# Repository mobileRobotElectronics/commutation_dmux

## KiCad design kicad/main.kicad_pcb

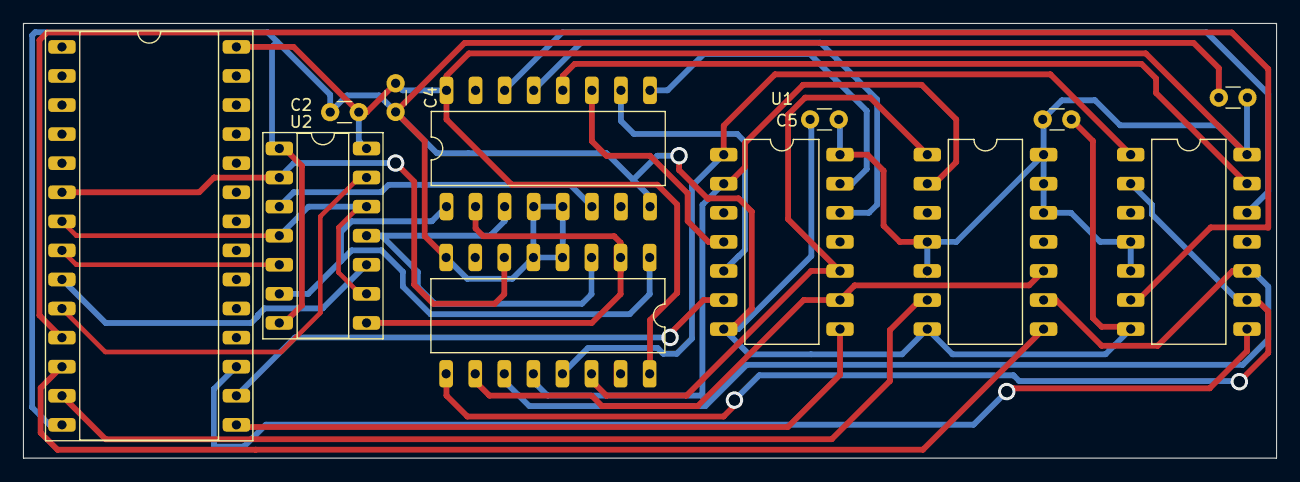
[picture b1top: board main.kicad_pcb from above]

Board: 2 copper layers, 109.5 x 38.0 mm, 12 parts (0 on the bottom side), 29 nets.

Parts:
C2, C3, C4, C5, C6: 100n; C_Disc_D3.0mm_W1.6mm_P2.50mm
J1: Conn_02x14_Counter_Clockwise; DIP-28_W15.24mm_Socket_LongPads
U1, U4, U5: 7421; DIP-14_W10.16mm_LongPads
U2: 74LS86; DIP-14_W7.62mm_Socket_LongPads
U3, U6: 74LS138; DIP-16_W10.16mm_LongPads

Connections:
+5V: C2.1, C3.1, C4.1, C5.1, C6.1, J1.28, U1.14 (VCC), U2.14 (VCC), U3.16 (VCC), U4.4, U4.5, U4.14 (VCC), U5.4, U5.5, U5.12, U5.13, U5.14 (VCC), U6.16 (VCC)
/B_H_OUT: J1.11, U4.6
/B_L_OUT: J1.15, U1.8
/DIR_IN: J1.7, U2.4, U2.9, U2.12
/G_H_OUT: J1.12, U5.8
/G_L_OUT: J1.16, U1.6
/H1_IN: J1.10, U2.13
/H2_IN: J1.9, U2.10
/H3_IN: J1.8, U2.5
/PWM_IN: J1.6, U2.2, U6.6 (G1)
/Y_H_OUT: J1.13, U5.6
/Y_L_OUT: J1.17, U4.8
/adressInverter/H1_OUT: U2.6, U3.1 (A0), U6.1 (A0)
/adressInverter/H2_OUT: U2.8, U3.2 (A1), U6.2 (A1)
/adressInverter/H3_OUT: U2.11, U3.3 (A2), U6.3 (A2)
/adressInverter//PWM: U2.3, U3.6 (G1)
GND: C2.2, C3.2, C4.2, C5.2, C6.2, J1.14, U1.7 (GND), U2.1, U2.7 (GND), U3.4 (~G2A), U3.5 (~G2B), U3.8 (GND), U4.7 (GND), U5.7 (GND), U6.4 (~G2A), U6.5 (~G2B), U6.8 (GND)
unnamed: U3.14 (~Y1), U4.12
unnamed: U1.12, U3.13 (~Y2)
unnamed: U3.12 (~Y3), U4.13
unnamed: U1.4, U3.11 (~Y4)
unnamed: U1.5, U3.10 (~Y5)
unnamed: U1.13, U3.9 (~Y6)
unnamed: U1.10, U5.1, U6.14 (~Y1)
unnamed: U1.1, U4.1, U6.13 (~Y2)
unnamed: U1.2, U5.2, U6.12 (~Y3)
unnamed: U4.10, U5.9, U6.11 (~Y4)
unnamed: U1.9, U5.10, U6.10 (~Y5)
unnamed: U4.2, U4.9, U6.9 (~Y6)

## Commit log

2023-10-06 initial commit, adding lsd template
2023-10-06 added gitignore
2023-10-06 added first design in cv file
2023-10-06 added schematic for demux
2023-10-06 finished footprints and started layout
2023-10-08 started layout for multiplexer
2023-10-08 added verilog implementation for commutation mux
2023-10-08 finished individual components layouts
2023-10-08 deleted unnecessary complexity
2023-10-09 fixed unreachable pin
2023-10-09 changed orientation of plug
2023-10-09 finished single dmux
2023-10-09 added reichelt bom
2023-10-09 final design
